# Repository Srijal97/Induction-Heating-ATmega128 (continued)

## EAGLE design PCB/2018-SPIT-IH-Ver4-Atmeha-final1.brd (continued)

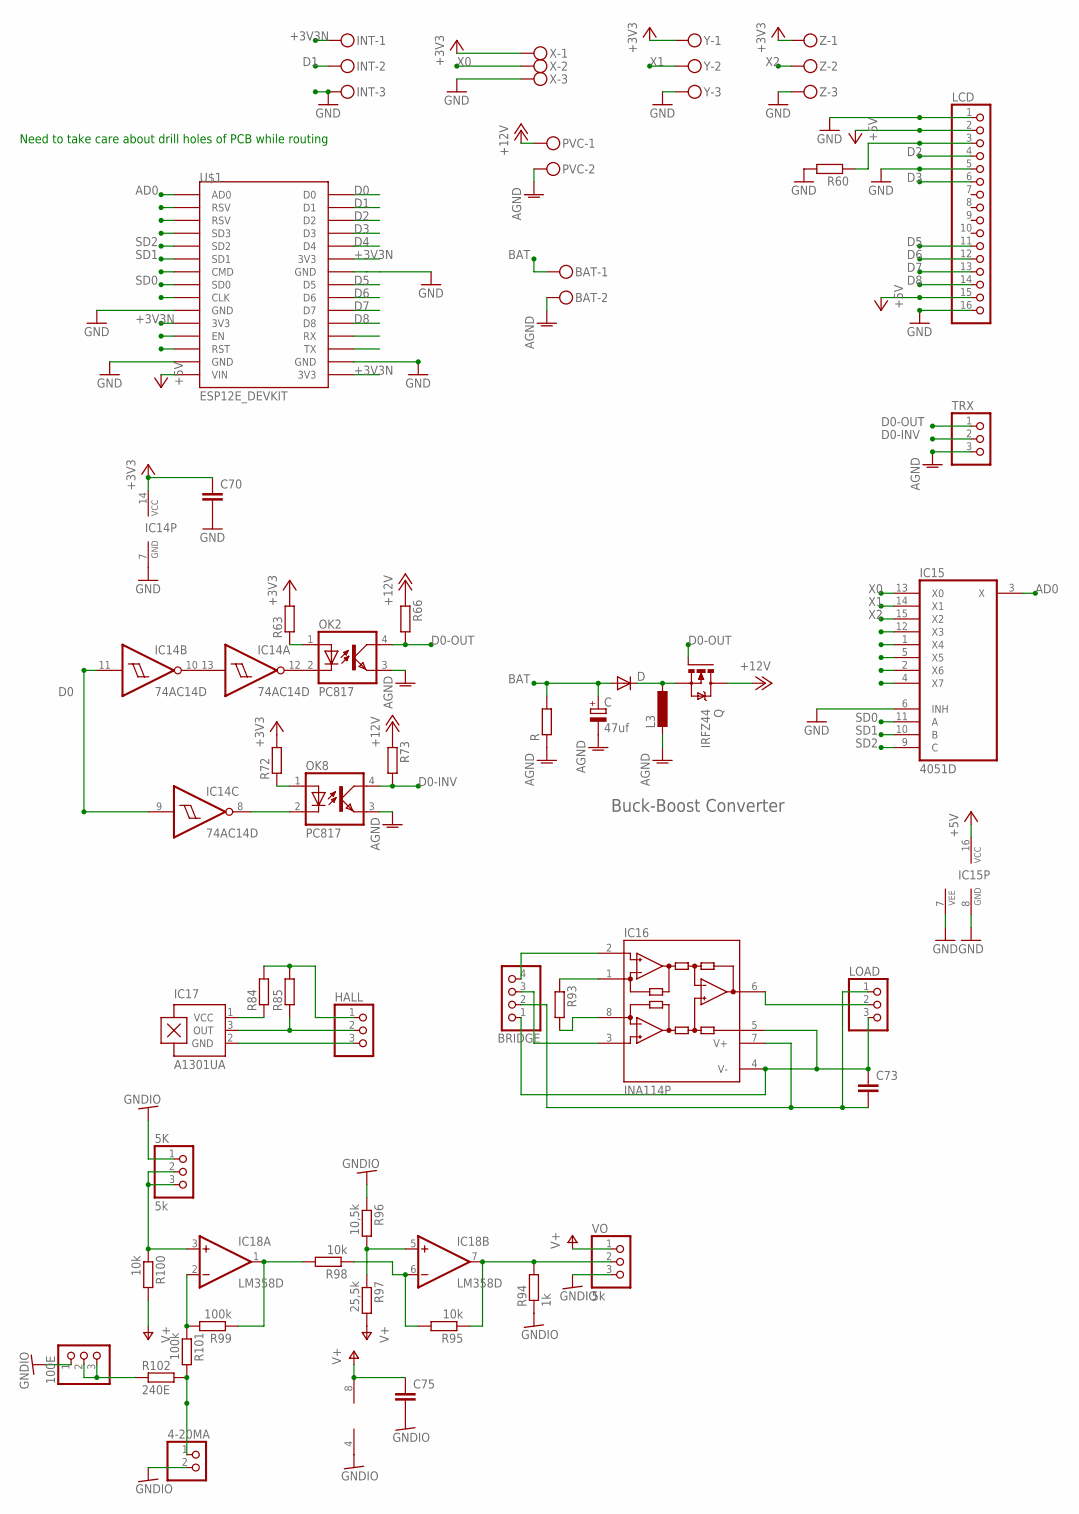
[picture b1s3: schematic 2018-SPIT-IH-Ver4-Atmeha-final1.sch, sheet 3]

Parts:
4-20MA: PINHD-1X2; 1X02
5K: 5k; 1X03
100E: 1X03
BAT: MKDSN1,5/2-5,08; MPN MKDSN 1,5/2-5.08
BRIDGE: PINHD-1X4; 1X04
C: 47uf; B45181A
C70, C73, C75: C-EUC1206; C1206
D: DO41-10
HALL: PINHD-1X3; 1X03
IC14: 74AC14D; SO14
IC15: 4051D; SO16
IC16: INA114P; DIL08
IC17: A1301UA; SIP3-UA
IC18: LM358D; SO08
INT: MKDSN1,5/3-5,08; MPN SMKDSN1,5/3-5,08
L3: L-EU0207/12; 0207/12
LCD: PINHD-1X16; 1X16
LOAD: PINHD-1X3; 1X03
OK2, OK8: PC817; DIL04; MPN PC817X4J000F
PVC: MKDSN1,5/2-5,08
Q: IRFZ44; TO220BV
R: R-EU_0207/10; 0207/10
R60, R63, R66, R72, R73, R84, R85, R93: R-EU_M1206; M1206
R94: 1k; M1206
R95, R98, R100: 10k; M1206
R96: 10,5k; M1206
R97: 25,5k; M1206
R99, R101: 100k; M1206
R102: 240E; M1206
TRX: PINHD-1X3; 1X03
U$1: ESP12E_DEVKIT
VO: 5k; 1X03
X: MKDSN1,5/3-5,08
Y: MKDSN1,5/3-5,08; MPN SMKDSN1,5/3-5,08
Z: MKDSN1,5/3-5,08; MPN SMKDSN1,5/3-5,08

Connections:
+3V3N: C70.1, IC14.14 (VCC), INT.1, R63.2, R72.2, U$1.3V3@0 (3V3), U$1.3V3@1 (3V3), U$1.3V3@2 (3V3), X.1, Y.1, Z.1
+5VN: IC15.16 (VCC), LCD.2, LCD.15, U$1.VIN
+12VN: PVC.1, Q.D, R66.1, R73.1
AD0: IC15.3 (X), U$1.AD0
BAT: BAT.1, C.+, D.A, R.2
D0: IC14.9 (I), IC14.11 (I), U$1.D0
D0-INV: OK8.4 (COL), R73.2, TRX.2
D0-OUT: OK2.4 (COL), Q.G, R66.2, TRX.1
D1: INT.2, U$1.D1
D2: LCD.4, U$1.D2
D3: LCD.6, U$1.D3
D4: U$1.D4
D5: LCD.11, U$1.D5
D6: LCD.12, U$1.D6
D7: LCD.13, U$1.D7
D8: LCD.14, U$1.D8
GNDIO: 4-20MA.2, 5K.1, 100E.1, C75.2, IC18.4 (V-), R94.1, R96.1, VO.3
unnamed: IC17.1 (VCC), R84.1
unnamed: HALL.2, IC17.3 (OUT), R85.1
unnamed: HALL.1, R84.2, R85.2
unnamed: HALL.3, IC17.2 (GND)
unnamed: IC18.1 (OUT), R98.2, R99.1
unnamed: IC18.2 (-IN), R99.2, R101.1
unnamed: LCD.3, R60.1
unnamed: OK2.1 (A), R63.1
unnamed: D.C, L3.1, Q.S
unnamed: OK8.1 (A), R72.1
unnamed: IC14.12 (O), OK2.2 (C)
unnamed: IC14.10 (O), IC14.13 (I)
unnamed: IC14.8 (O), OK8.2 (C)
unnamed: BRIDGE.1, C73.1, IC16.4 (V-), IC16.5 (REF), LOAD.3
unnamed: IC16.6 (OUT), LOAD.2
unnamed: BRIDGE.2, C73.2, IC16.7 (V+), LOAD.1
unnamed: IC16.1 (RG), R93.1
unnamed: IC16.8 (RG), R93.2
unnamed: BRIDGE.4, IC16.2 (-IN)
unnamed: BRIDGE.3, IC16.3 (+IN)
unnamed: IC18.7 (OUT), R94.2, R95.1, VO.2
unnamed: IC18.6 (-IN), R95.2, R98.1
unnamed: IC18.5 (+IN), R96.2, R97.1
unnamed: 5K.2, 5K.3, IC18.3 (+IN), R100.1
unnamed: 4-20MA.1, R101.2, R102.2
unnamed: 100E.2, 100E.3, R102.1
NAGND: BAT.2, C.-, L3.2, OK2.3 (EMIT), OK8.3 (EMIT), PVC.2, R.1, TRX.3
NGND: C70.2, IC14.7 (GND), IC15.6 (INH), IC15.7 (VEE), IC15.8 (GND), INT.3, LCD.1, LCD.5, LCD.16, R60.2, U$1.GND@0 (GND), U$1.GND@1 (GND), U$1.GND@2 (GND), U$1.GND@3 (GND), X.3, Y.3, Z.3
SD0: IC15.11 (A), U$1.SD0
SD1: IC15.10 (B), U$1.SD1
SD2: IC15.9 (C), U$1.SD2
V+: C75.1, IC18.8 (V+), R97.2, R100.2, VO.1
X0: IC15.13 (X0), X.2
X1: IC15.14 (X1), Y.2
X2: IC15.15 (X2), Z.2

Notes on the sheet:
Buck-Boost Converter
Need to take care about drill holes of PCB while routing

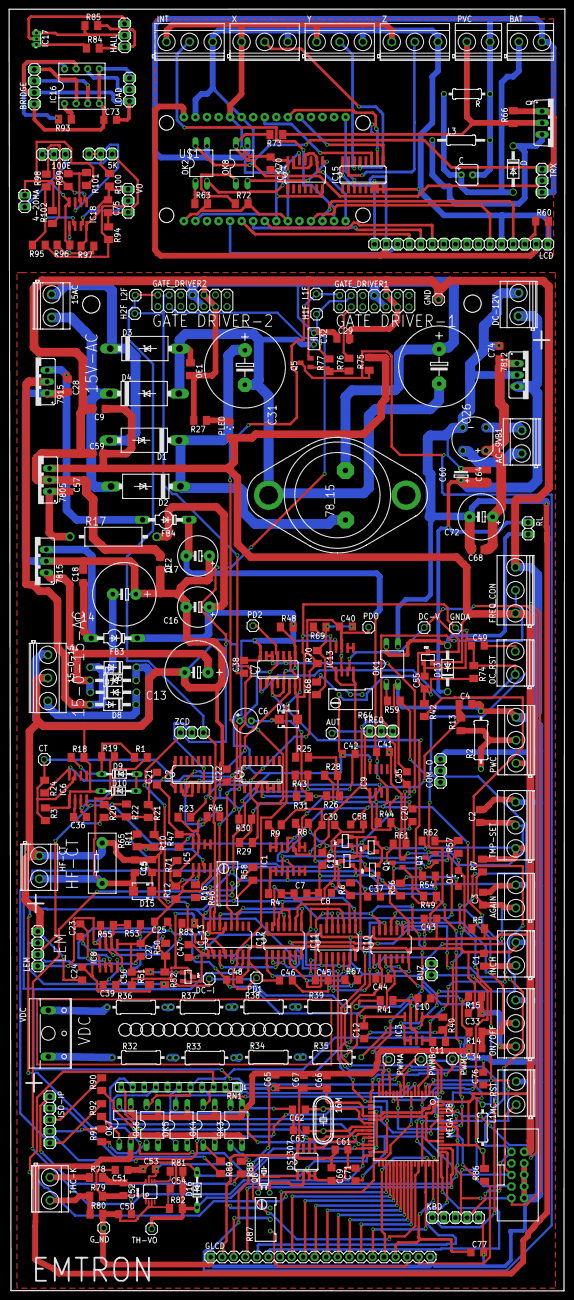
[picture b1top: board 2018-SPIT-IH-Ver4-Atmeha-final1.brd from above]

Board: 2 copper layers, 122.2 x 281.8 mm, 314 parts (0 on the bottom side), 231 nets.

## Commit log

2019-11-06 Revamped and working code, installed at Riddhi Heatron
